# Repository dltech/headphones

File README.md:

# headphones
Bluetooth A2DP profile headphones using Ti CC2640 SOC
TODO: 
*everything

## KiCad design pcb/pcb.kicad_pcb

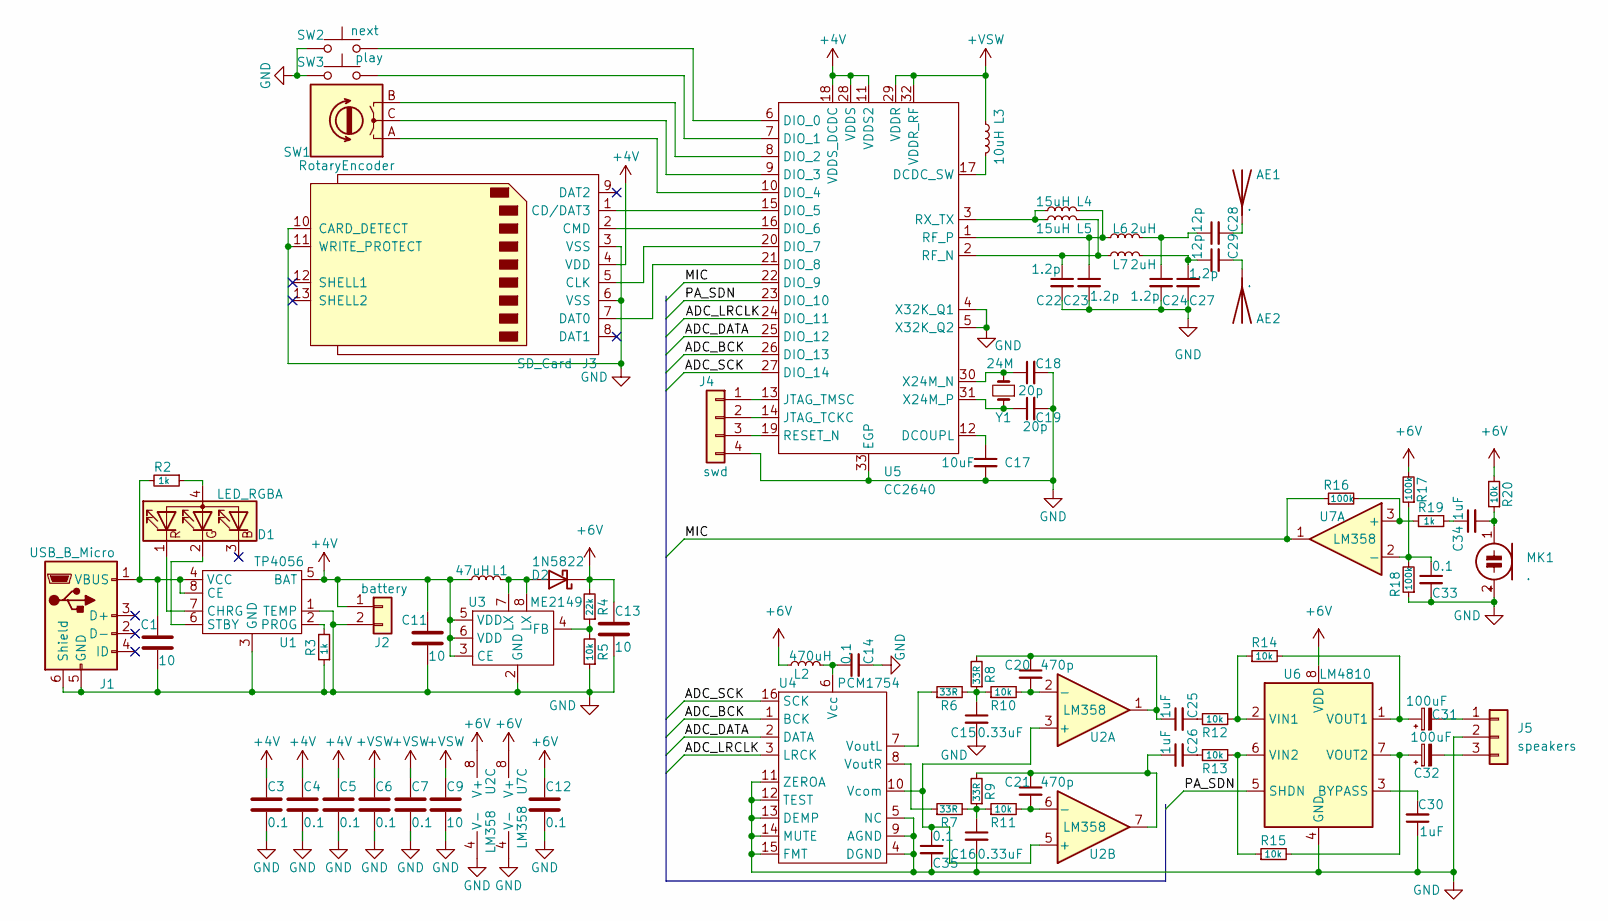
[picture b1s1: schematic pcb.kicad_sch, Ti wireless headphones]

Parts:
AE1, AE2: .; SolderWirePad_1x01_SMD_1x2mm
C1, C9, C11, C13: 10; C_0805_2012Metric
C3, C4, C5, C6, C7, C12, C14, C33, C35: 0.1; C_0402_1005Metric
C15, C16: 0.33uF; C_0603_1608Metric
C17: 10uF; C_0805_2012Metric
C18, C19: 20p; C_0402_1005Metric
C20, C21: 470p; C_0603_1608Metric
C22, C23, C24, C27: 1.2p; C_0603_1608Metric
C25, C26, C30, C34: 1uF; C_0805_2012Metric
C28, C29: 12p; C_0603_1608Metric
C31, C32: 100uF; CP_EIA-3216-10_Kemet-I
D1: LED_RGBA; LED_Cree-PLCC4_3.2x2.8mm_CCW
D2: 1N5822; D_SMA
J1: USB_B_Micro; USB_Micro-B_Amphenol_10104110_Horizontal
J2: battery; PinHeader_1x02_P2.54mm_Vertical
J3: SD_Card; SD_Hirose_DM1AA_SF_PEJ82
J4: swd
J5: speakers; PinHeader_1x03_P2.54mm_Vertical
L1: 47uH; L_1206_3216Metric
L2: 470uH; L_0603_1608Metric
L3: 10uH; L_0603_1608Metric
L4, L5: 15uH; L_0603_1608Metric
L6, L7: 2uH; L_0603_1608Metric
MK1: .; CP_Radial_D5.0mm_P2.50mm
R2, R3, R19: 1k; R_0402_1005Metric
R4: 22k; R_0805_2012Metric
R5, R10, R11, R12, R13, R14, R15, R20: 10k; R_0402_1005Metric
R6, R7, R8, R9: 33R; R_0402_1005Metric
R16, R17, R18: 100k; R_0402_1005Metric
SW1: RotaryEncoder; mouse_encoder
SW2: next; SW_PUSH_6mm
SW3: play; SW_PUSH_6mm
U1: TP4056; SOP-8_3.9x4.9mm_P1.27mm
U2, U7: LM358; SOIC-8_3.9x4.9mm_P1.27mm
U3: ME2149; SOP-8_3.9x4.9mm_P1.27mm
U4: PCM1754; SSOP-16_5.3x6.2mm_P0.65mm
U5: CC2640; HVQFN-32-1EP_5x5mm_P0.5mm_EP3.1x3.1mm
U6: LM4810; TSSOP-8_3x3mm_P0.65mm
Y1: 24M; Crystal_SMD_5032-2Pin_5.0x3.2mm

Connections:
+4V: C3.1, C4.1, C5.1, C11.1, J2.1, J3.4 (VDD), L1.1, U1.5 (BAT), U3.3 (CE), U3.5 (VDD), U3.6 (VDD), U5.11 (VDDS2), U5.18 (VDDS_DCDC), U5.28 (VDDS)
+6V: C12.1, C13.1, D2.1 (K), L2.1, R4.2, R17.2, R20.2, U2.8 (V+), U6.8 (VDD), U7.8 (V+); also elsewhere on the board
+VSW: C6.1, C7.1, C9.1, L3.1, U5.29 (VDDR), U5.32 (VDDR_RF)
/ADC_BCK: U4.1 (BCK), U5.26 (DIO_13)
/ADC_DATA: U4.2 (DATA), U5.25 (DIO_12)
/ADC_LRCLK: U4.3 (LRCK), U5.24 (DIO_11)
/ADC_SCK: U4.16 (SCK), U5.27 (DIO_14)
/MIC: R16.1, U5.22 (DIO_9), U7.1
/PA_SDN: U5.23 (DIO_10), U6.5 (SHDN)
GND: C1.2, C3.2, C4.2, C5.2, C6.2, C7.2, C9.2, C11.2, C12.2, C13.2, C14.2, C15.2, C16.2, C17.2, C18.2, C19.2, C22.2, C23.2, C24.2, C27.2, C30.1, C33.2, C35.2, J1.5 (GND), J1.6 (Shield), J2.2, J3.3 (VSS), J3.6 (VSS), J3.10 (CARD_DETECT), J3.11 (WRITE_PROTECT), J4.4, J5.2, MK1.2 (+), R3.1, R5.1, R18.1, SW2.1, SW3.1, U1.1 (TEMP), U1.3 (GND), U2.4 (V-), U3.2 (GND), U4.4 (DGND), U4.5 (NC), U4.9 (AGND), U4.11 (ZEROA), U4.12 (TEST), U4.13 (DEMP), U4.14 (MUTE), U4.15 (FMT), U5.4 (X32K_Q1), U5.5 (X32K_Q2), U5.33 (EGP), U6.4 (GND), U7.4 (V-); also elsewhere on the board
unnamed: AE1.1 (A), C28.2
unnamed: AE2.1 (A), C29.2
unnamed: C1.1, J1.1 (VBUS), R2.2, U1.4 (VCC), U1.8 (CE)
unnamed: C14.1, L2.2, U4.6 (Vcc)
unnamed: C15.1, R6.2, R8.1, R10.1
unnamed: C16.1, R7.2, R9.1, R11.1
unnamed: C17.1, U5.12 (DCOUPL)
unnamed: C18.1, U5.30 (X24M_N), Y1.2
unnamed: C19.1, U5.31 (X24M_P), Y1.1
unnamed: C20.1, C25.1, R8.2, U2.1
unnamed: C20.2, R10.2, U2.2 (-)
unnamed: C21.1, C26.1, R9.2, U2.7
unnamed: C21.2, R11.2, U2.6 (-)
unnamed: C22.1, L5.1, L7.2, U5.2 (RF_N)
unnamed: C23.1, L4.1, L6.2, U5.1 (RF_P)
unnamed: C24.1, C28.1, L6.1
unnamed: C25.2, R12.1
unnamed: C26.2, R13.1
unnamed: C27.1, C29.1, L7.1
unnamed: C30.2, U6.3 (BYPASS)
unnamed: C31.1, R14.2, U6.1 (VOUT1)
unnamed: C31.2, J5.1
unnamed: C32.1, R15.2, U6.7 (VOUT2)
unnamed: C32.2, J5.3
unnamed: C33.1, R17.1, R18.2, U7.2 (-)
unnamed: C34.1, R19.2
unnamed: C34.2, MK1.1 (-), R20.1
unnamed: C35.1, U2.3 (+), U2.5 (+), U4.10 (Vcom)
unnamed: D1.1 (RK), U1.7 (CHRG)
unnamed: D1.2 (GK), U1.6 (STBY)
unnamed: D1.4 (A), R2.1
unnamed: D2.2 (A), L1.2, U3.7 (LX), U3.8 (LX)
unnamed: J3.1 (CD/DAT3), U5.15 (DIO_5)
unnamed: J3.7 (DAT0), U5.21 (DIO_8)
unnamed: J4.1, U5.13 (JTAG_TMSC)
unnamed: J4.2, U5.14 (JTAG_TCKC)
unnamed: J4.3, U5.19 (RESET_N)
unnamed: L3.2, U5.17 (DCDC_SW)
unnamed: L4.2, L5.2, U5.3 (RX_TX)
unnamed: R3.2, U1.2 (PROG)
unnamed: R4.1, R5.2, U3.4 (FB)
unnamed: R6.1, U4.7 (VoutL)
unnamed: R7.1, U4.8 (VoutR)
unnamed: R12.2, R14.1, U6.2 (VIN1)
unnamed: R13.2, R15.1, U6.6 (VIN2)
unnamed: R16.2, R19.1, U7.3 (+)
unnamed: SW1.A, U5.10 (DIO_4)
unnamed: SW1.B, U5.8 (DIO_2)
unnamed: SW1.C, U5.9 (DIO_3)
unnamed: SW2.2, U5.6 (DIO_0)
unnamed: SW3.2, U5.7 (DIO_1)
unnamed: J3.2 (CMD), U5.16 (DIO_6)
unnamed: J3.5 (CLK), U5.20 (DIO_7)

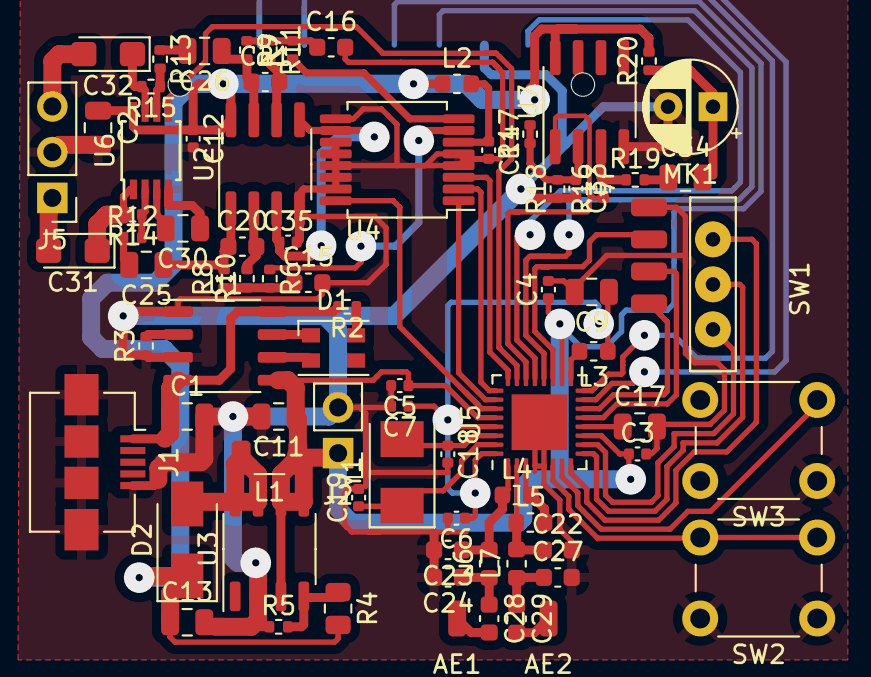
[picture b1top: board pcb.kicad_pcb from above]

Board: 2 copper layers, 80 parts (1 on the bottom side), 63 nets.

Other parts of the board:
C2: 10; C_0805_2012Metric

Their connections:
+6V: C2.1; also elsewhere on the board
GND: C2.2; also elsewhere on the board

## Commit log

2022-04-27 doc obtained
2022-04-27 readme
2022-04-30 memorymap
2022-05-05 gpio regs
2022-05-07 i2s reg names
2022-05-08 i2s regs
2022-05-10 event reg
2022-05-12 radio regs
2022-05-13 flash regs started
2022-05-13 flash regs
2022-05-15 2640 sch component
2022-05-17 factory config reg almost
2022-05-17 factory config reg
2022-05-18 power regs
2022-05-18 timer regs
2022-05-18 rtc regs
2022-05-18 wdt regs
2022-05-19 all reg addresses
2022-05-19 all crypto regs
2022-05-19 all rnd regs
2022-05-19 all aux regs
2022-05-20 all uart regs
2022-05-20 all ssi regs
2022-05-20 all i2c regs
2022-05-20 all regs
2022-05-21 schematic
2022-05-21 schematic png
2022-05-23 pcb footprints
2022-05-24 pcb block wiev
2022-05-26 4.5x4 pcb
